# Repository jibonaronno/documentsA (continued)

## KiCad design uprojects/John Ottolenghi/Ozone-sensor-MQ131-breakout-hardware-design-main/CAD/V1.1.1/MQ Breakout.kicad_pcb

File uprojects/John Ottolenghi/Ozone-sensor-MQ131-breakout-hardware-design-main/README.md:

# Ozone sensor MQ131 breakout Hardware Design

## About the Product

|  |
| :----------------------------------------------------------: |
| [Buy Ozone sensor MQ131 breakout](https://www.solde.red/333110) |

The MQ131 sensor’s sensitivity and selectivity enable it to effectively detect and measure ozone levels, making it a valuable tool for applications such as air quality monitoring, ozone generators, and ozone leakage detection systems. By integrating the MQ131 sensor with appropriate electronic circuits and microcontrollers like Dasduino, you can create systems that provide real-time ozone concentration monitoring and trigger alerts when hazardous levels are detected.

The breakout board works with both digital (DO) and analog signals (AO). The digital output is obtained by setting a threshold value with a potentiometer. The analog output will differ depending on the intensity of the gas.

---

## Repository Contents

This repository contains all design files for Ozone sensor MQ131 breakout, organized as follows:

- **`CAD` folder**: Contains KiCAD design files, including:
  - Schematics
  - PCB layout
  - Panel PCB layout
  - Source 3D files in Fusion360, if any
  - All files are sorted by version with a detailed change log.
- **`OUTPUTS` folder**: Includes all production-ready files, such as:
  - Bill of Materials (BOM) and interactive BOM (iBOM)
  - PDF versions of schematics
  - 3D `.step` file of the board
  - 3D-printable models
  - Gerber files for PCB manufacturing
  - Image of the pinout of the board
  - Product image
  - Compliance, legal and generic sales documents

Refer to the `Change Log` in the CAD folder for details about updates between versions.

---

## Learn More About the Product

Beyond the repository, explore the following resources:

### Soldered Verify

The **Soldered Verify** system ensures every board you purchase from Soldered is fully functional. It also provides access to exclusive test data for your product. To get started, find the unique Soldered Verify ID on your product's packaging and enter the ID on the [Soldered Verify page](https://soldered.com/verify/) to access test results and additional product details.

### Soldered Community

Soldered Community is your go-to place for technical support. Our engineers track and answer all questions posted there, and it’s a great space for the maker community. Get answers to your questions and solutions for your challenges at [Soldered Community](https://soldered.com/community).

### solde.red

solde.red is an ultimate URL shortener and information hub. Access it by typing solde.red/ followed by your product SKU, e.g., [solde.red/333000](https://solde.red/333000), to find getting-started guides, datasheets, open-source hardware and software files, certifications, images, pinouts, and more. Read more about the shortener [here](https://solde.red/info/).

---

## Contributing

Contributions are welcome! Here’s how you can get involved:

- Submit pull requests to enhance the design or fix issues.
- Report bugs or problems by opening an issue.

We encourage community collaboration to make this product even better.

---

## About Soldered

[Soldered for Makers](https://soldered.com) specializes in designing and manufacturing electronic products tailored for enthusiasts, ranging from hobbyists to professionals. Our portfolio includes electronic boards, sensors, and actuators that are widely utilized in fields such as microelectronics, mechatronics, robotics, programming, and IoT. Every product we offer is designed in-house and built upon open-source hardware and software platforms. Proudly certified and manufactured within the European Union, our catalog likely includes the product you need for your project.

We complement these products with comprehensive tutorials and manuals, product descriptions, schematics, programming codes, and project examples. Our round-the-clock [customer and technical support](https://soldered.com/community) is available for all our products, irrespective of the sales channel. Soldered’s success and services reflect our maker community’s unwavering [trust](https://www.trustpilot.com/review/soldered.com), for which we are deeply grateful. Join our community and create using Soldered products.

---

## License

All Soldered open-source hardware (OSH) is under The TAPR Open Hardware License. Read more in the LICENSE file located in this repository.

**Disclaimer:**

No warranty - all designs in this repository are distributed in the hope that they will be useful, but without any warranty. They are provided "AS IS", therefore without warranty of any kind, either expressed or implied. The entire quality and performance of what you do with the contents of this repository are your responsibility. In no event Soldered Electronics will be liable for your damages, or losses, including any general, special, incidental, or consequential damage arising out of the use or inability to use the contents of this repository. 

---

## Have fun!

Thank you for your support from your fellow makers at Soldered Electronics.

Happy Making!

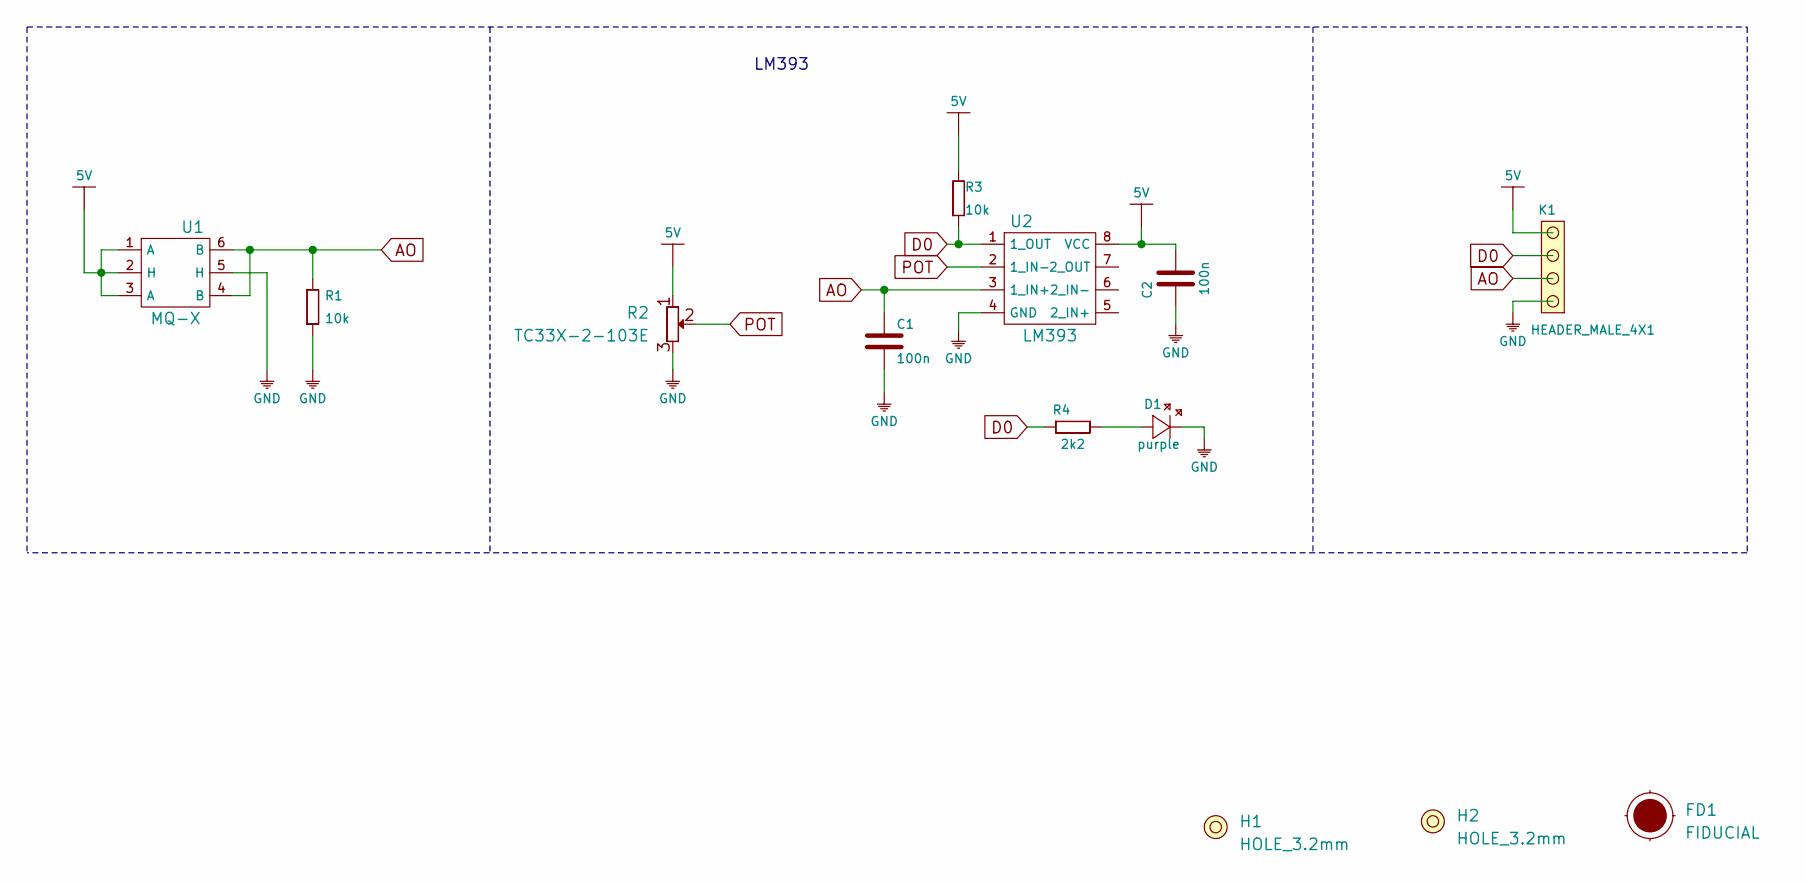
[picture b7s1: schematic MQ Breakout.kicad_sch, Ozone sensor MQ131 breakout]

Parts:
C1, C2: 100n; 0603C
D1: purple; 0402LED
FD1: FIDUCIAL; FIDUCIAL_23
H1, H2: HOLE_3.2mm
K1: HEADER_MALE_4X1
R1, R3: 10k; 0603R
R2: TC33X-2-103E; tc33x-2-103e
R4: 2k2; 0402R
U1: MQ-X; MQ
U2: LM393; SOIC−8

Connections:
5V: C2.2, K1.4, R2.1, R3.2, U1.1 (A), U1.2 (H), U1.3 (A), U2.8 (VCC)
AO: C1.2, K1.2, R1.2, U1.4 (B), U1.6 (B), U2.3 (1_IN+)
D0: K1.3, R3.1, R4.1, U2.1 (1_OUT)
GND: C1.1, C2.1, D1.2 (K), K1.1, R1.1, R2.3, U1.5 (H), U2.4 (GND)
unnamed: D1.1 (A), R4.2
POT: R2.2, U2.2 (1_IN-)

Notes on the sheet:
LM393

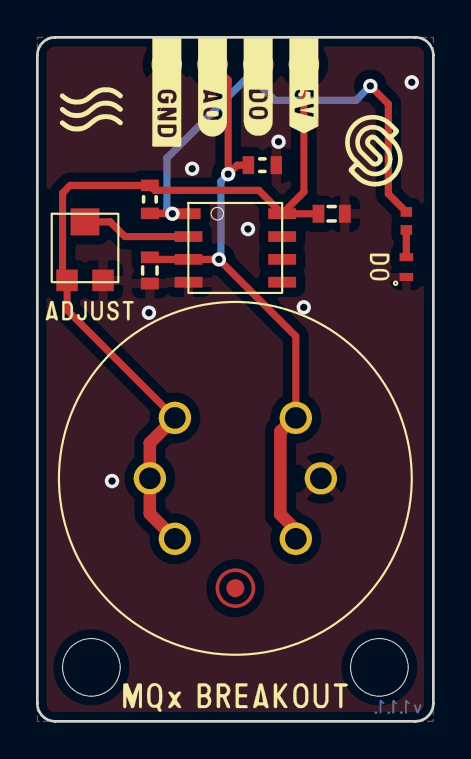
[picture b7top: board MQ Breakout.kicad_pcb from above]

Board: 2 copper layers, 22.0 x 38.0 mm, 13 parts (1 on the bottom side), 6 nets.

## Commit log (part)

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2025-02-25 25 FEB 25 Office
2025-02-26 26 FEB 25 Office
2025-02-28 28 FEB 25 Office
2025-03-01 update from home 1-mar-2025
2025-03-05 5 mar 25 Office
2025-03-06 6 mar 25 Office
2025-03-07 7 mar 25 Office
2025-03-11 12-Mar-25 Dorm
2025-03-12 12 Mar 25
2025-03-13 13 Mar 25
2025-03-13 14 Mar 2025 Dorm
2025-03-14 14 Mar 25
2025-03-16 16 Mar 2025 Dorm
2025-03-19 19 Mar 25
2025-03-20 20 Mar 25
2025-03-23 23 Mar 2025 Dorm
2025-03-25 26 Mar 2025 Dorm
2025-03-26 26 MAR 25
2025-03-27 27 MAR 25
2025-03-27 28 Mar 2025 Dorm
2025-03-28 28 Mar 25
2025-04-08 8 Apr 25
2025-04-10 10 Apr 25
2025-04-11 11 Apr 25
2025-04-15 15 Apr 25
2025-04-16 16 Apr 25
2025-04-17 17 Apr 25
2025-04-20 20 April 2025 Dorm
2025-04-22 22 Apr 25
2025-04-22 22 April 2025 Dorm
2025-04-25 25 Apr 25
2025-04-27 27 April 2025 Dorm
2025-05-15 15 May 25
2025-05-25 25 May 25
2025-05-25 25 May 2025 Dorm
2025-05-26 26 May 2025 Dorm
2025-05-28 28 May 25
2025-05-30 30 May 25
2025-06-01 1 June 2025 Dorm
2025-06-03 3 June 2025 Dorm
2025-06-11 11 JUN 25 Office
2025-06-15 15 June 2025 Dorm
2025-06-17 15 june 25 Office
2025-06-20 20 june 25 Office
2025-06-26 25 June 25 Office
2025-06-26 26 June 25 Office
2025-06-30 30 June 25 Office
2025-07-02 2.1 July 25 Office
2025-07-03 3 July 25 Office
2025-07-06 06 July 2025 Dorm
2025-07-07 7 July 25 Office
2025-07-10 10 July 25 Office
2025-07-14 14 July 25 Office
2025-07-15 15 July 25 Office
2025-07-15 15 July 2025 Dorm
2025-07-17 17 July 25 Office
2025-07-17 17 July 2025 Dorm
2025-07-18 18 July 2025 Sanion
2025-07-18 18 July 2025 Dorm
2025-07-20 21 July 2025 Dorm
2025-07-21 21 July 2025 Sanion
2025-07-22 22 July 2025 Sanion
2025-07-23 23 July 2025 Sanion
2025-07-24 24 July 25 Office
2025-07-27 27 July 2025 Dorm
2025-07-30 31 July 2025 Dorm
2025-08-01 2 Aug 2025 Dorm
2025-08-04 4 Aug 2025 Dorm 01
2025-08-05 5 Aug 2025 Dorm
2025-08-06 6 Aug 2025 Dorm
2025-08-06 6 Aug 2025 Dorm 1
2025-08-10 10 Aug 2025 Dorm 1
2025-08-14 14 Aug 2025 Daejeon 1
2025-08-15 15 Aug 2025 Dorm 1
2025-08-19 19 Aug 2025 Dorm 1
2025-08-25 25 Aug 2025 Dorm 1
2025-08-26 26 Aug 2025 Dorm
2025-09-02 2 Sept 25 Office
2025-09-02 2 Sept Home
2025-09-04 4 Sept 25 Office
2025-09-05 5 Sept 25 Office
2025-09-08 8 Sept 25 Office
2025-09-09 9 Sept Home
2025-09-11 11 Sept 25 Office
2025-09-14 14 Sept Home
2025-09-16 16 Sept 25 Office
2025-09-17 17 Sept 25 Office
2025-09-19 19 Sept 25 Office
2025-09-21 22 Sep 2025 home
2025-09-22 22 Sept 25 Office
2025-09-23 23 Sept 25 Office
2025-09-24 24 Sept 25 Office
2025-09-25 25 Sept 25 Office
2025-09-26 26 Sept 25 Office
2025-09-28 28 Sep 2025 home
2025-09-29 29 Sept 25 Office
2025-09-30 30 Sept 25 Office
2025-09-30 30 Sep 2025 home
2025-10-12 Oleksii Correction Updates Oct-13-25 Dorm
2025-10-12 blk'
2025-10-13 13 Oct 25 Office
2025-10-15 14 Oct 25 Office
2025-10-15 15 Oct 25 Office
2025-10-16 16 Oct 25 Office
2025-10-17 17 Oct 25 Office
2025-10-19 Weekly Report Update 19Oct25
2025-10-24 24 Oct 25 Office
2025-10-26 Weekly Report Update 26-Oct-25
2025-10-27 27 Oct 25 Office
2025-10-28 28 Oct 25 Office
2025-10-29 29 Oct 25 Office
2025-10-30 30 Oct 25 Office
2025-10-31 31 Oct 25 Office
2025-11-05 5 Nov 25 Office
2025-11-06 Nov-6-25 Cheongsol
2025-11-07 7 Nov 25 Office
2025-11-09 Nov-11-25 Cheongsol
2025-11-11 1 Nov 25 Office
2025-11-13 13 Nov 25 Office
2025-11-14 14 Nov 25 Office
2025-11-19 19 Nov 25 Office
2025-11-24 24 Nov 25 Office
2025-12-02 2 Dec 25 Office
2025-12-10 10 Dec 25 Office
2025-12-10 Updates 10-dec-25
2025-12-12 13 Dec 25 Office
2025-12-15 15 Dec 25 Office
2025-12-16 16 Dec 25 Office
2025-12-18 18 Dec 25 Office
2025-12-19 19 Dec 25 Office
2025-12-22 22 Dec 25 Office
2025-12-23 23 Dec 25 Office
2025-12-24 24 Dec 25 Office
2025-12-28 Updates 28-dec-25
2025-12-29 29 Dec 25 Office
2026-01-04 Updates 04-Jan-25
2026-01-05 05 Jan 2026 Office
2026-01-05 Updates 05-Jan-2026
2026-01-06 06 Jan 26 Office
2026-01-06 Updates 06-Jan-26 home
2026-01-07 Upate From Home Mac 07 Jan 2026
2026-01-08 08 Jan 26 Office
2026-01-11 Upate From Home Mac 12 Jan 2026
2026-01-13 13 Jan 26 Office
2026-01-14 Updates 14-jan-26
2026-01-15 15 Jan 26 Office
2026-01-15 Updates 16-jan-26
2026-01-16 16 Jan 26 Office
2026-01-18 Updates 19-Jan-25
2026-01-19 19 Jan 26 Office
2026-01-20 20 Jan 26 Office
2026-01-20 Updates 20-Jan-25
2026-01-23 23 Jan 26 Office
2026-01-23 Updates 23-Jan-25 home
2026-01-25 Upate From Home Mac 26 Jan 2026
2026-01-26 26 Jan 26 Office
2026-01-27 27 Jan 26
2026-01-27 Ignore lock files
2026-01-28 28 Jan 26
2026-01-28 Upate From Home Mac 28 Jan 2026
2026-01-29 Update 29 Jan 2026
2026-01-29 Upate From Home Mac 29 Jan 2026
2026-01-30 Update 30 Jan 2026
2026-02-01 update 02-Feb-2026
2026-02-02 Update 2 Feb 2026
2026-02-02 update 03-Feb-2026
2026-02-03 Update 3 Feb 2026
2026-02-04 Update 4 Feb 2026
2026-02-05 Update 5 Feb 2026
2026-02-06 Update 6 Feb 2026
2026-02-09 Update 9 Feb 2026
2026-02-10 Update 10 Feb 2026
2026-02-10 update 10-Feb-2026
2026-02-11 Update 11 Feb 2026
2026-02-12 Update 12 Feb 2026
2026-02-13 Update 13 Feb 2026
2026-02-20 Update 20 Feb 2026
2026-02-23 Update 23 Feb 2026
2026-02-23 local update 23 feb 26
2026-02-24 Update 24 Feb 2026
2026-02-26 Update 26 Feb 2026
2026-02-26 local update 26 feb 26
2026-03-02 local update 2 Mar 26
2026-03-03 Update 3 mar 2026
2026-03-04 Update 4 mar 2026
2026-03-05 Update 5 mar 2026
2026-03-06 Update 7 mar 2026
2026-03-08 updates dorm 08 Mar 26
2026-03-09 Update 9 mar 2026
2026-03-10 Update 10 mar 2026
2026-03-11 Update 11 mar 2026
2026-03-12 Update 12 mar 2026
2026-03-13 Update 13 mar 2026
2026-03-14 local update 14 Mar 26
2026-03-14 Update Ubuntu 14 2026
2026-03-15 local update 15 Mar 26
2026-03-17 Update 17 mar 2026
2026-03-18 Update 18 mar 2026
2026-03-19 Update 19 mar 2026
2026-03-19 local update 19 Mar 26
2026-03-22 local update 22 Mar 26
2026-03-23 Update 23 mar 2026
2026-03-23 local update 24 Mar 26
2026-03-24 Update 24 mar 2026
2026-03-25 Update 25 mar 2026
2026-03-25 Update Ubuntu 25 Mar 2026
2026-03-26 Update 26 mar 2026
2026-03-27 Update 27 mar 2026
2026-03-30 Update 30 mar 2026
2026-03-31 Update 31 mar 2026
2026-04-02 Update 2 Apr 2026
2026-04-03 Update 3 Apr 2026
2026-04-06 Update 6 Apr 2026
2026-04-06 local update 06 APR 26
2026-04-07 Update 7 Apr 2026
2026-04-09 Update 9 Apr 2026
2026-04-09 local update 09 APR 26
2026-04-10 Update 10 Apr 2026
2026-04-13 Update 13 Apr 2026
2026-04-14 Update 14 Apr 2026
2026-04-15 Update 15 Apr 2026
2026-04-19 local update 19 APR 26
2026-04-20 Update 20 Apr 2026
2026-04-21 Update 21 Apr 2026
2026-04-22 Update 22 Apr 2026
2026-04-23 Update 23 Apr 2026
2026-04-26 local update 26 APR 26
2026-04-27 Update 27 Apr 2026
2026-04-27 Meshlite PCB 001 Update
2026-04-28 Update 28 Apr 2026
2026-04-29 Update 29 Apr 2026
2026-04-30 Update 30 Apr 2026
2026-05-06 Update 06 May 2026
2026-05-07 Meshlite PCB 002 Update
2026-05-07 Update 07 May 2026
2026-05-07 local update 07 MAY 26
2026-05-08 Update 08 May 2026
2026-05-09 local update 09 MAY 26
2026-05-10 Update 11 May 2026
2026-05-12 Update 12 May 2026
2026-05-12 local update 12 MAY 26
2026-05-13 Update 13 May 2026
2026-05-14 Update 14 May 2026
2026-05-17 local update 17 MAY 26
2026-05-18 Update 18 May 2026
2026-05-20 Update 20 May 2026
2026-05-21 Update 21 May 2026
2026-05-22 Update 22 May 2026
2026-05-24 local update 24 MAY 26
2026-05-25 ROOM 25 MAY 2026 Updates
2026-05-26 Update 26 May 2026
2026-05-27 Update 28 May 2026
2026-05-27 27 May 26 Room
2026-05-28 ROOM 28 MAY 2026 Updates
2026-05-28 local update 28 MAY 26
2026-05-29 Update 29 May 2026
2026-05-30 local update 30 MAY 26
2026-05-31 ROOM 1 June 2026 Updates
2026-06-01 Update 1 June 2026
2026-06-01 Update 2 June 2026
2026-06-03 ROOM 3 June 2026 Updates
2026-06-04 Update 4 June 2026
2026-06-05 Update 5 June 2026
2026-06-07 ROOM 7 June 2026 Updates
2026-06-08 Update 8 June 2026
2026-06-09 Update 9 June 2026
2026-06-10 Update 10 June 2026
2026-06-11 Update 11 June 2026
2026-06-15 Update 15 June 2026
2026-06-22 Update 22 June 2026
2026-06-23 Update 23 June 2026
2026-06-25 Update 25 June 2026
2026-06-26 Update 26 June 2026
2026-06-29 Update 29 June 2026
2026-06-30 Update 30 June 2026
